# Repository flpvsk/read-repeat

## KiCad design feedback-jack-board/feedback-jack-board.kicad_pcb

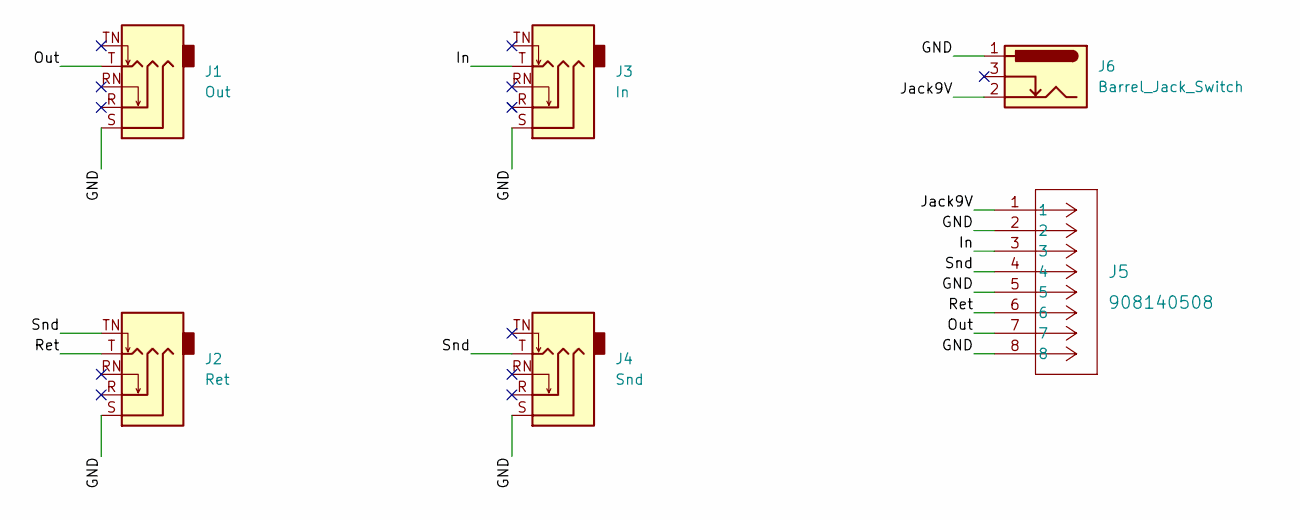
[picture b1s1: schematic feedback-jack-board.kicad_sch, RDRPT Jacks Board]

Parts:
J1: Out; tayda-A6446-6mm35-jack-pcb-compact
J2: Ret; tayda-A6446-6mm35-jack-pcb-compact
J3: In; tayda-A6446-6mm35-jack-pcb-compact
J4: Snd; tayda-A6446-6mm35-jack-pcb-compact
J5: 908140508; CONN_SDA-90814_08_MOL
J6: Barrel_Jack_Switch; BarrelJack_GCT_DCJ200-10-A_Horizontal

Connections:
/GND: J1.S, J2.S, J3.S, J4.S, J5.2, J5.5, J5.8, J6.1
/In: J3.T, J5.3
/Jack9V: J5.1, J6.2
/Out: J1.T, J5.7
/Ret: J2.T, J5.6
/Snd: J2.TN, J4.T, J5.4

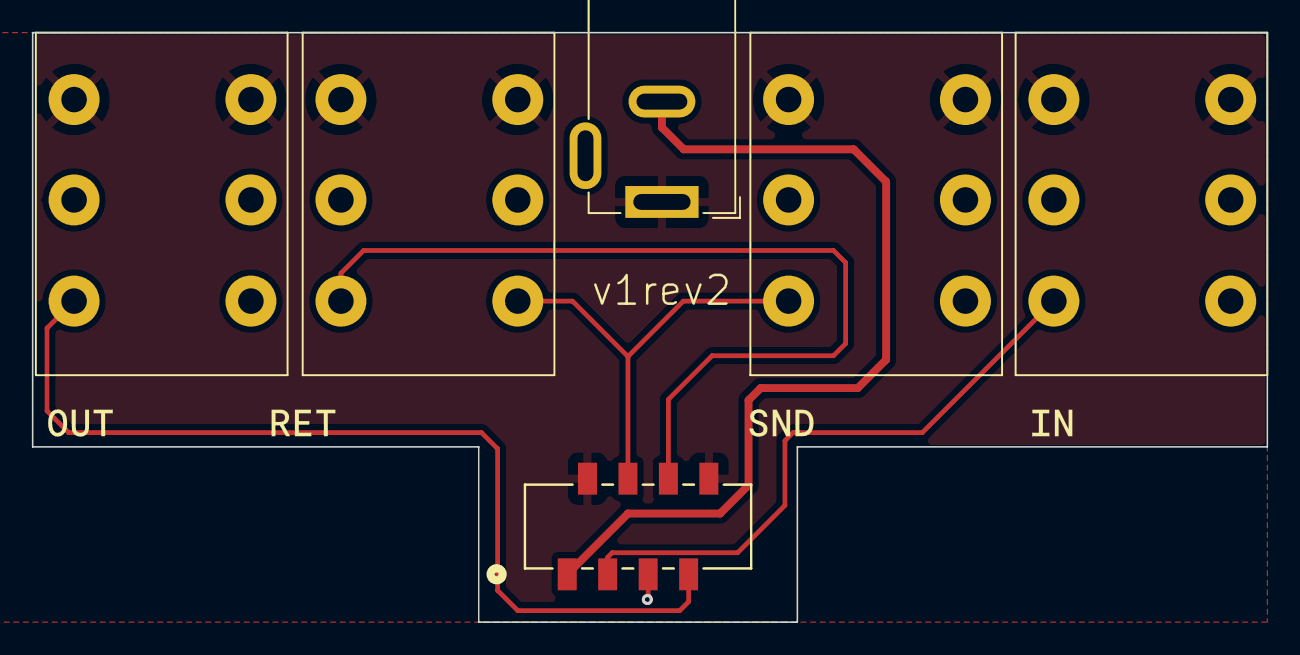
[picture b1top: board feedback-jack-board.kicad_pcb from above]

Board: 2 copper layers, 77.5 x 37.0 mm, 11 parts (1 on the bottom side), 6 nets.

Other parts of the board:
kibuzzard-67A4F1E7: G***; kibuzzard-67A4F1E7
kibuzzard-67A4F12B: G***; kibuzzard-67A4F12B
kibuzzard-67A4F13A: G***; kibuzzard-67A4F13A
kibuzzard-67A4F113: G***; kibuzzard-67A4F113
kibuzzard-67A4F143: G***; kibuzzard-67A4F143

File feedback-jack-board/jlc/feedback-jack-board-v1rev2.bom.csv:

"Comment","Designator","Footprint","LCSC"
"Out","J1","Tayda-A6446-6-35mm-Compact-PCB-Mounted-Jack:tayda-A6446-6mm35-jack-pcb-compact",""
"Ret","J2","Tayda-A6446-6-35mm-Compact-PCB-Mounted-Jack:tayda-A6446-6mm35-jack-pcb-compact",""
"In","J3","Tayda-A6446-6-35mm-Compact-PCB-Mounted-Jack:tayda-A6446-6mm35-jack-pcb-compact",""
"Snd","J4","Tayda-A6446-6-35mm-Compact-PCB-Mounted-Jack:tayda-A6446-6mm35-jack-pcb-compact",""
"908140508","J5","molex-picoflex8:CONN_SDA-90814_08_MOL",""
"Barrel_Jack_Switch","J6","Connector_BarrelJack:BarrelJack_GCT_DCJ200-10-A_Horizontal",""

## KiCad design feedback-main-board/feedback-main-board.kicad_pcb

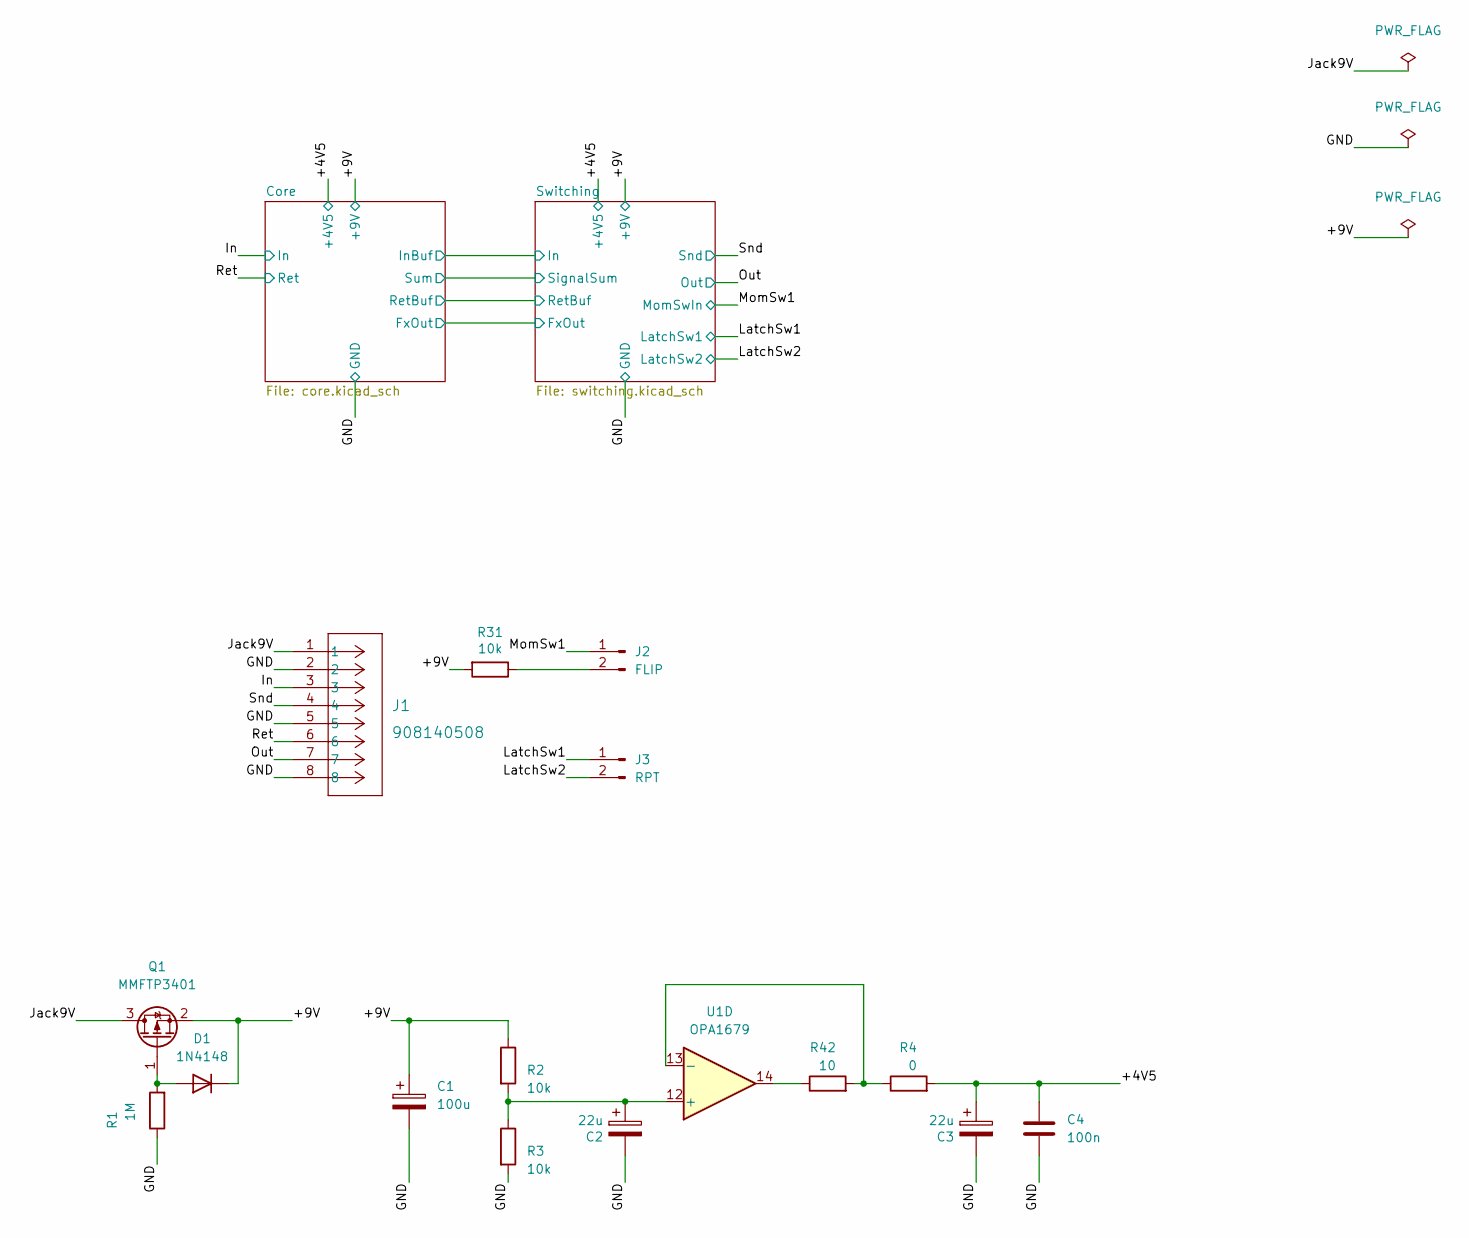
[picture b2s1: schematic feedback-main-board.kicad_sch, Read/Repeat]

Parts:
C1: 100u; CP_Elec_6.3x5.4; LCSC C2836437
C2, C3: 22u; CP_Elec_5x5.4; LCSC C23289
C4: 100n; C_0603_1608Metric_Pad1.08x0.95mm_HandSolder; Mouser 581-06035C105MAT2A
D1: 1N4148; D_SOD-323_HandSoldering; LCSC C6423741
J1: 908140508; CONN_SDA-90814_08_MOL; LCSC DNP
J2: FLIP; JST_XH_B2B-XH-A_1x02_P2.50mm_Vertical; LCSC DNP
J3: RPT; JST_XH_B2B-XH-A_1x02_P2.50mm_Vertical; LCSC DNP
Q1: MMFTP3401; SOT-23; LCSC C596234
R1: 1M; R_0603_1608Metric_Pad0.98x0.95mm_HandSolder; LCSC C22935
R2, R3, R31: 10k; R_0603_1608Metric_Pad0.98x0.95mm_HandSolder; LCSC C25804
R4: 0; R_0603_1608Metric_Pad0.98x0.95mm_HandSolder; LCSC C21189
R42: 10; R_0603_1608Metric_Pad0.98x0.95mm_HandSolder; LCSC C22859
U1: OPA1679; SOIC-14_3.9x8.7mm_P1.27mm; LCSC C2878631

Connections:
/+4V5: C3.1, C4.2, R4.2; also elsewhere on the board
/+9V: C1.1, D1.1 (K), Q1.2 (S), R2.1, R31.2; also elsewhere on the board
/GND: C1.2, C2.2, C3.2, C4.1, J1.2, J1.5, J1.8, R1.1, R3.2; also elsewhere on the board
/In: J1.3; also elsewhere on the board
/Jack9V: J1.1, Q1.3 (D)
/LatchSw1: J3.1; also elsewhere on the board
/LatchSw2: J3.2; also elsewhere on the board
/MomSw1: J2.1; also elsewhere on the board
/Out: J1.7; also elsewhere on the board
/Ret: J1.6; also elsewhere on the board
/Snd: J1.4; also elsewhere on the board
unnamed: D1.2 (A), Q1.1 (G), R1.2
unnamed: J2.2, R31.1
unnamed: R42.1, U1.14
unnamed: C2.1, R2.2, R3.1, U1.12 (+)
unnamed: R4.1, R42.2, U1.13 (-)

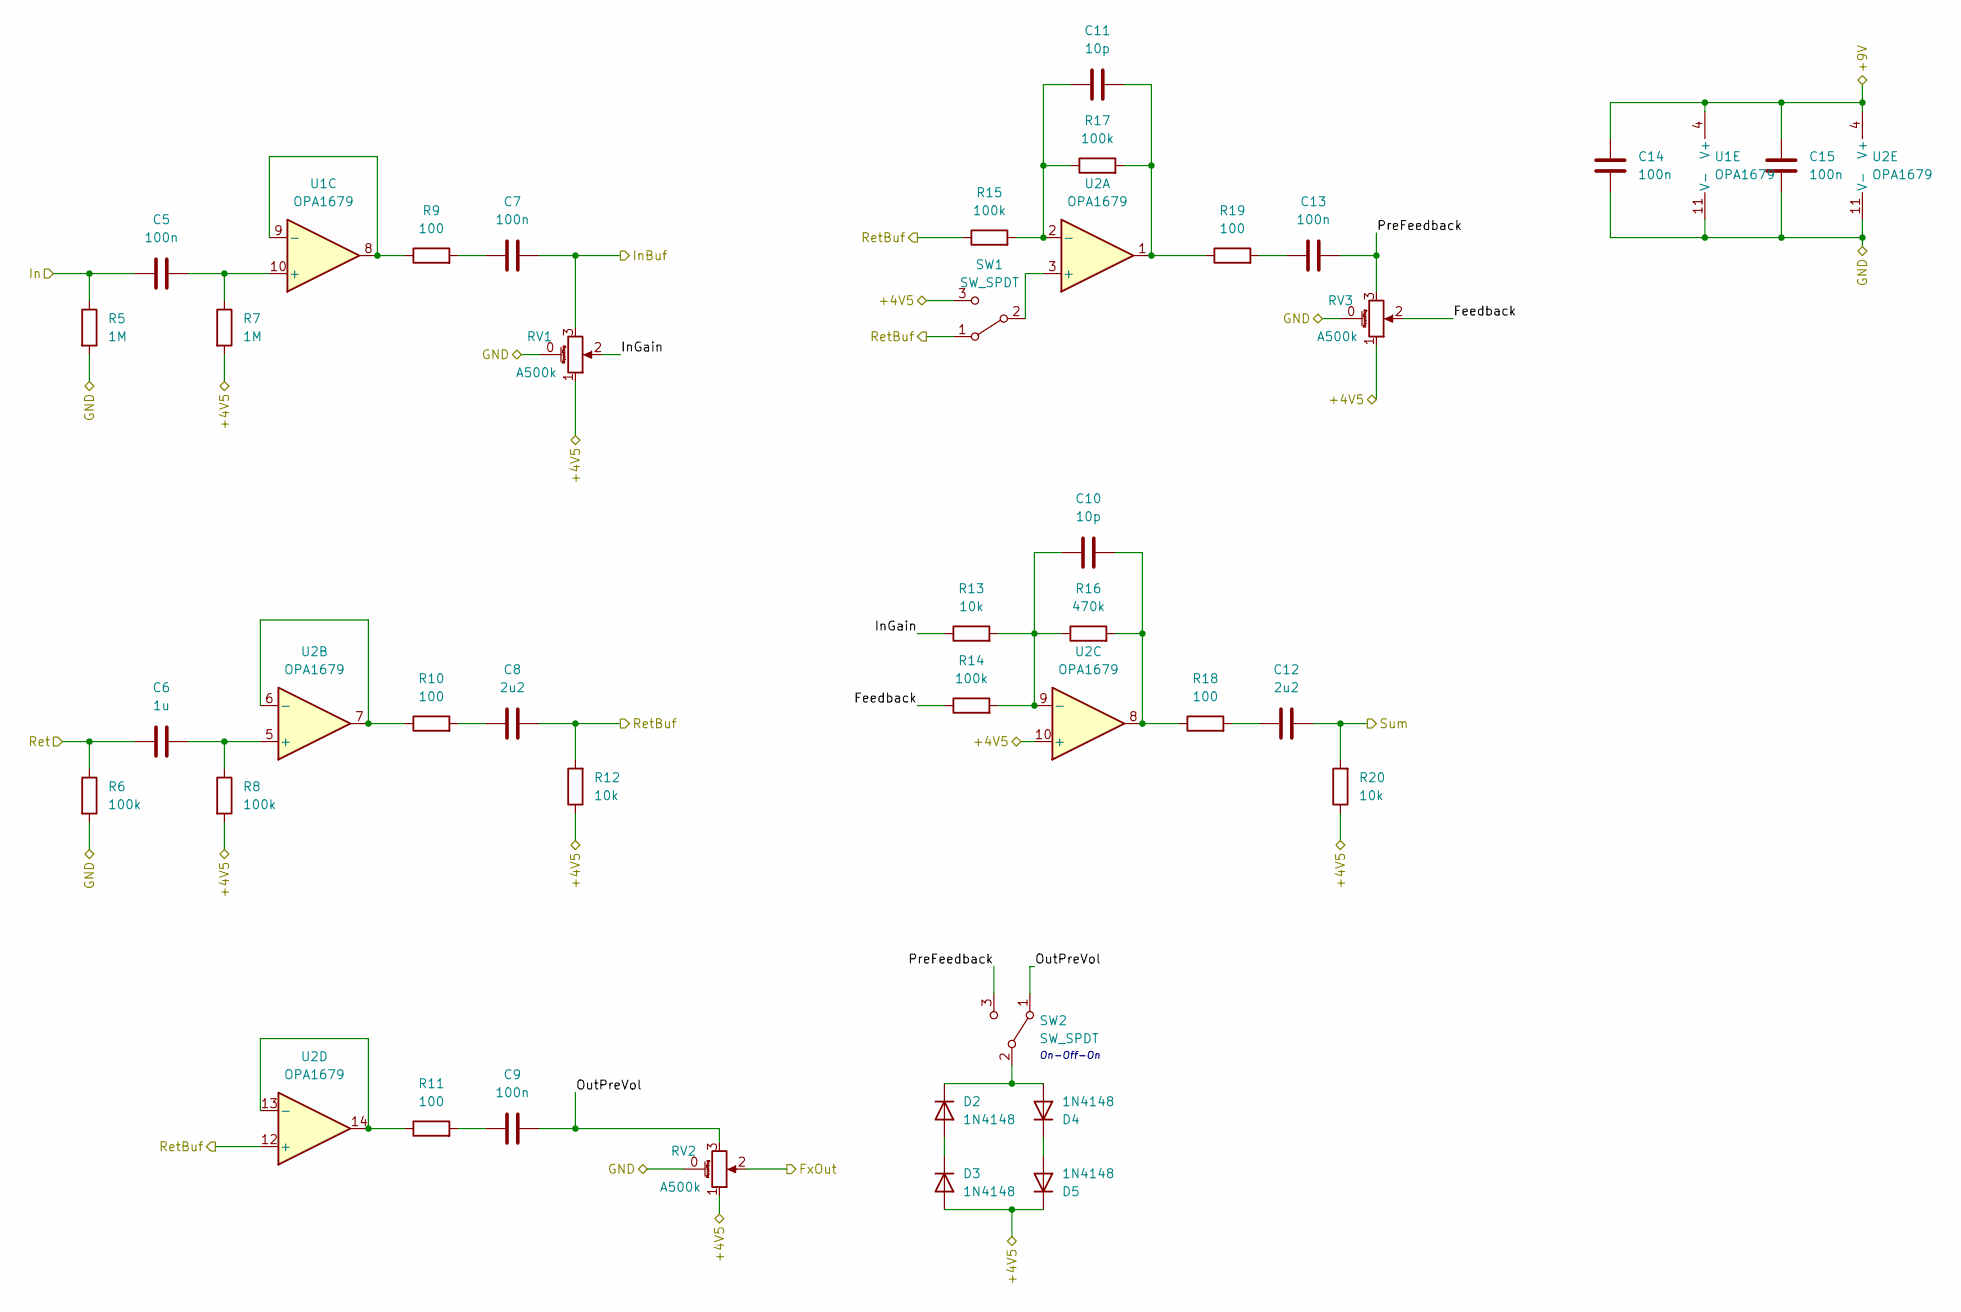
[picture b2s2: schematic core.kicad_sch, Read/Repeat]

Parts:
C5: 100n; C_Rect_L7.0mm_W2.5mm_P5.00mm; LCSC DNP
C6: 1u; C_Rect_L7.0mm_W4.5mm_P5.00mm; Mouser 505-MKS2-1/63/10A
C7, C9, C13: 100n; C_Rect_L7.2mm_W7.2mm_P5.00mm_FKS2_FKP2_MKS2_MKP2; Mouser 505-MKS22.2/63/5
C8, C12: 2u2; C_Rect_L7.2mm_W7.2mm_P5.00mm_FKS2_FKP2_MKS2_MKP2; Mouser 505-MKS22.2/63/5
C10, C11: 10p; C_0603_1608Metric_Pad1.08x0.95mm_HandSolder; LCSC C1634
C14, C15: 100n; C_0603_1608Metric_Pad1.08x0.95mm_HandSolder; Mouser 581-06035C105MAT2A
D2, D3, D4, D5: 1N4148; D_SOD-323; LCSC C2128
R5, R7: 1M; R_0603_1608Metric_Pad0.98x0.95mm_HandSolder; LCSC C22935
R6, R8, R14, R15, R17: 100k; R_0603_1608Metric_Pad0.98x0.95mm_HandSolder; LCSC C25803
R9, R10, R11, R18, R19: 100; R_0603_1608Metric_Pad0.98x0.95mm_HandSolder; LCSC C22775
R12, R13, R20: 10k; R_0603_1608Metric_Pad0.98x0.95mm_HandSolder; LCSC C25804
R16: 470k; R_0603_1608Metric_Pad0.98x0.95mm_HandSolder; LCSC C23178
RV1, RV2, RV3: A500k; V3_TRIM_R0904NB10KL-Keepout; LCSC DNP
SW1, SW2: SW_SPDT; SPDT.LUGS.PM; LCSC DNP
U1, U2: OPA1679; SOIC-14_3.9x8.7mm_P1.27mm; LCSC C2878631

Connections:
/+4V5: D3.2 (A), D5.1 (K), R7.2, R8.2, R12.1, R20.1, RV1.1, RV2.1, RV3.1, SW1.3 (C), U2.10 (+); also elsewhere on the board
/+9V: C14.2, C15.2, U1.4 (V+), U2.4 (V+); also elsewhere on the board
/Core/Feedback: R14.1, RV3.2
/Core/FxOut: RV2.2; also elsewhere on the board
/Core/InBuf: C7.2, RV1.3; also elsewhere on the board
/Core/InGain: R13.1, RV1.2
/Core/OutPreVol: C9.2, RV2.3, SW2.1 (A)
/Core/PreFeedback: C13.2, RV3.3, SW2.3 (C)
/Core/RetBuf: C8.2, R12.2, R15.1, SW1.1 (A), U2.12 (+); also elsewhere on the board
/Core/Sum: C12.2, R20.2; also elsewhere on the board
/GND: C14.1, C15.1, R5.2, R6.2, RV1.0 (ShieldPin), RV2.0 (ShieldPin), RV3.0 (ShieldPin), U1.11 (V-), U2.11 (V-); also elsewhere on the board
/In: C5.1, R5.1; also elsewhere on the board
/Ret: C6.1, R6.1; also elsewhere on the board
unnamed: C7.1, R9.2
unnamed: C8.1, R10.2
unnamed: C9.1, R11.2
unnamed: C10.2, R16.2, R18.1, U2.8
unnamed: C11.2, R17.2, R19.1, U2.1
unnamed: C12.1, R18.2
unnamed: C13.1, R19.2
unnamed: D2.2 (A), D3.1 (K)
unnamed: D2.1 (K), D4.2 (A), SW2.2 (B)
unnamed: D4.1 (K), D5.2 (A)
unnamed: SW1.2 (B), U2.3 (+)
unnamed: C5.2, R7.1, U1.10 (+)
unnamed: R9.1, U1.8, U1.9 (-)
unnamed: C11.1, R15.2, R17.1, U2.2 (-)
unnamed: C6.2, R8.1, U2.5 (+)
unnamed: R10.1, U2.6 (-), U2.7
unnamed: C10.1, R13.2, R14.2, R16.1, U2.9 (-)
unnamed: R11.1, U2.13 (-), U2.14

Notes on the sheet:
On-Off-On

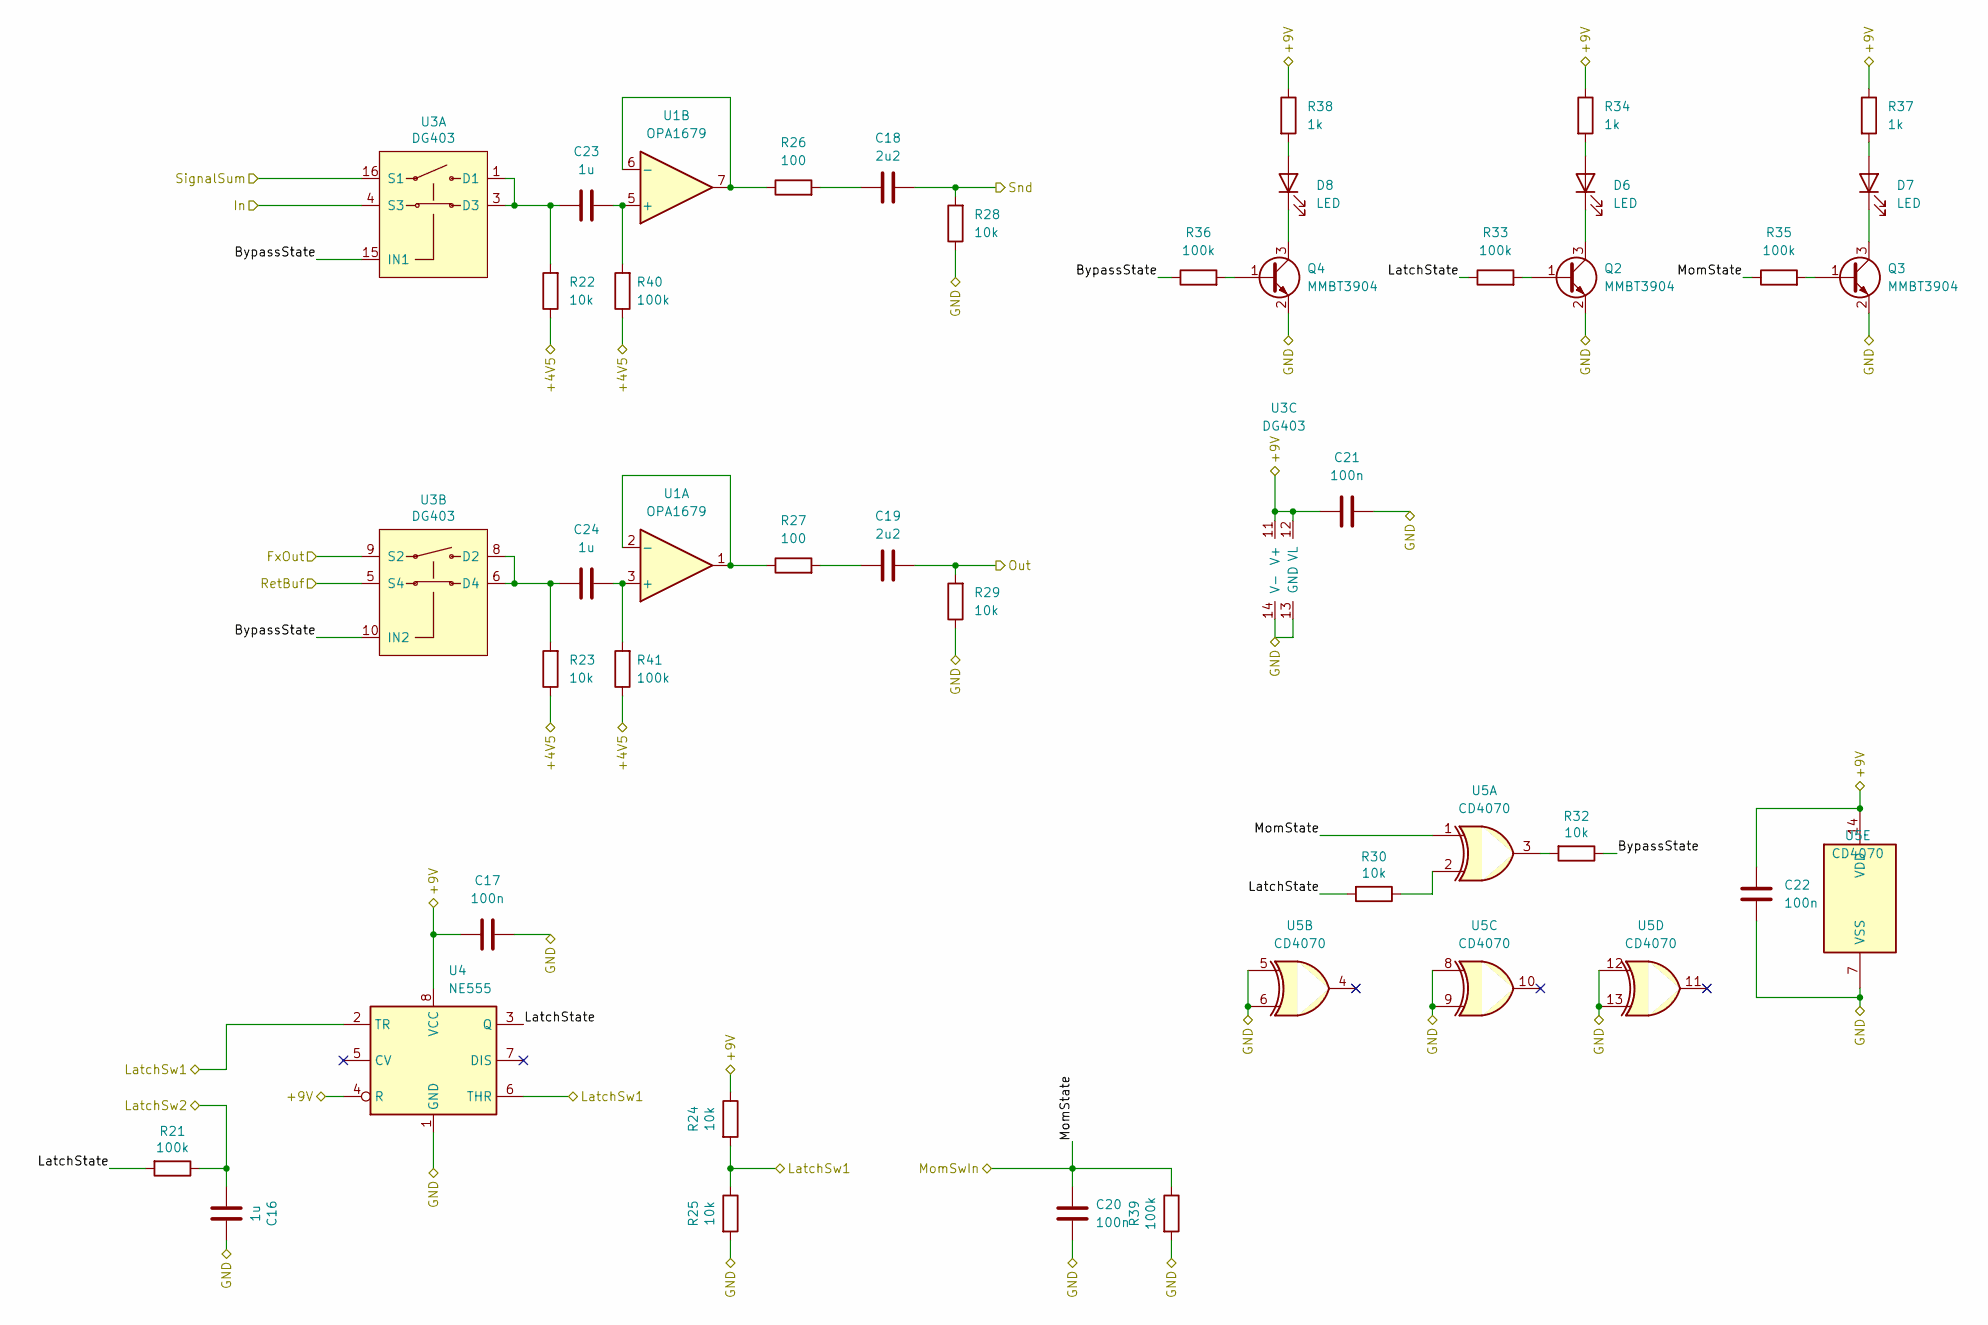
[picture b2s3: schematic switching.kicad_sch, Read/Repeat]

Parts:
C16: 1u; C_0603_1608Metric_Pad1.08x0.95mm_HandSolder; Mouser 581-06035C105MAT2A
C17, C20, C21, C22: 100n; C_0603_1608Metric_Pad1.08x0.95mm_HandSolder; Mouser 581-06035C105MAT2A
C18, C19: 2u2; C_Rect_L7.2mm_W7.2mm_P5.00mm_FKS2_FKP2_MKS2_MKP2; Mouser 505-MKS22.2/63/5
C23, C24: 1u; C_Rect_L7.0mm_W2.5mm_P5.00mm; LCSC DNP
D6, D7, D8: LED; LED_D5.0mm; LCSC DNP
Q2, Q3, Q4: MMBT3904; SOT-23; LCSC C20526
R21, R33, R35, R36, R39, R40, R41: 100k; R_0603_1608Metric_Pad0.98x0.95mm_HandSolder; LCSC C25803
R22, R23, R24, R25, R28, R29, R30, R32: 10k; R_0603_1608Metric_Pad0.98x0.95mm_HandSolder; LCSC C25804
R26, R27: 100; R_0603_1608Metric_Pad0.98x0.95mm_HandSolder; LCSC C22775
R34, R37, R38: 1k; R_0603_1608Metric_Pad0.98x0.95mm_HandSolder; LCSC C21190
U1: OPA1679; SOIC-14_3.9x8.7mm_P1.27mm; LCSC C2878631
U3: DG403; SOIC-16_3.9x9.9mm_P1.27mm; LCSC C145284
U4: NE555; SOIC-8_3.9x4.9mm_P1.27mm; LCSC C7593
U5: CD4070; SOIC-14_3.9x8.7mm_P1.27mm; Mouser 595-CD4070BM96E4

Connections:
/+4V5: R22.1, R23.1, R40.1, R41.1; also elsewhere on the board
/+9V: C17.1, C21.1, C22.2, R24.1, R34.1, R37.1, R38.1, U3.11 (V+), U3.12 (VL), U4.4 (R), U4.8 (VCC), U5.14 (VDD); also elsewhere on the board
/Core/FxOut: U3.9 (S2); also elsewhere on the board
/Core/InBuf: U3.4 (S3); also elsewhere on the board
/Core/RetBuf: U3.5 (S4); also elsewhere on the board
/Core/Sum: U3.16 (S1); also elsewhere on the board
/GND: C16.1, C17.2, C20.2, C21.2, C22.1, Q2.2 (E), Q3.2 (E), Q4.2 (E), R25.2, R28.1, R29.1, R39.2, U3.13 (GND), U3.14 (V-), U4.1 (GND), U5.5, U5.6, U5.7 (VSS), U5.8, U5.9, U5.12, U5.13; also elsewhere on the board
/LatchSw1: R24.2, R25.1, U4.2 (TR), U4.6 (THR); also elsewhere on the board
/LatchSw2: C16.2, R21.1; also elsewhere on the board
/MomSw1: C20.1, R35.1, R39.1, U5.1; also elsewhere on the board
/Out: C19.2, R29.2; also elsewhere on the board
/Snd: C18.2, R28.2; also elsewhere on the board
/Switching/BypassState: R32.1, R36.1, U3.10 (IN2), U3.15 (IN1)
/Switching/LatchState: R21.2, R30.2, R33.1, U4.3 (Q)
unnamed: C18.1, R26.2
unnamed: C19.1, R27.2
unnamed: D6.2 (A), R34.2
unnamed: D6.1 (K), Q2.3 (C)
unnamed: D7.2 (A), R37.2
unnamed: D7.1 (K), Q3.3 (C)
unnamed: D8.2 (A), R38.2
unnamed: D8.1 (K), Q4.3 (C)
unnamed: Q2.1 (B), R33.2
unnamed: Q3.1 (B), R35.2
unnamed: Q4.1 (B), R36.2
unnamed: R30.1, U5.2
unnamed: R32.2, U5.3
unnamed: C24.2, R41.2, U1.3 (+)
unnamed: R27.1, U1.1, U1.2 (-)
unnamed: C23.2, R40.2, U1.5 (+)
unnamed: R26.1, U1.6 (-), U1.7
unnamed: C23.1, R22.2, U3.1 (D1), U3.3 (D3)
unnamed: C24.1, R23.2, U3.6 (D4), U3.8 (D2)

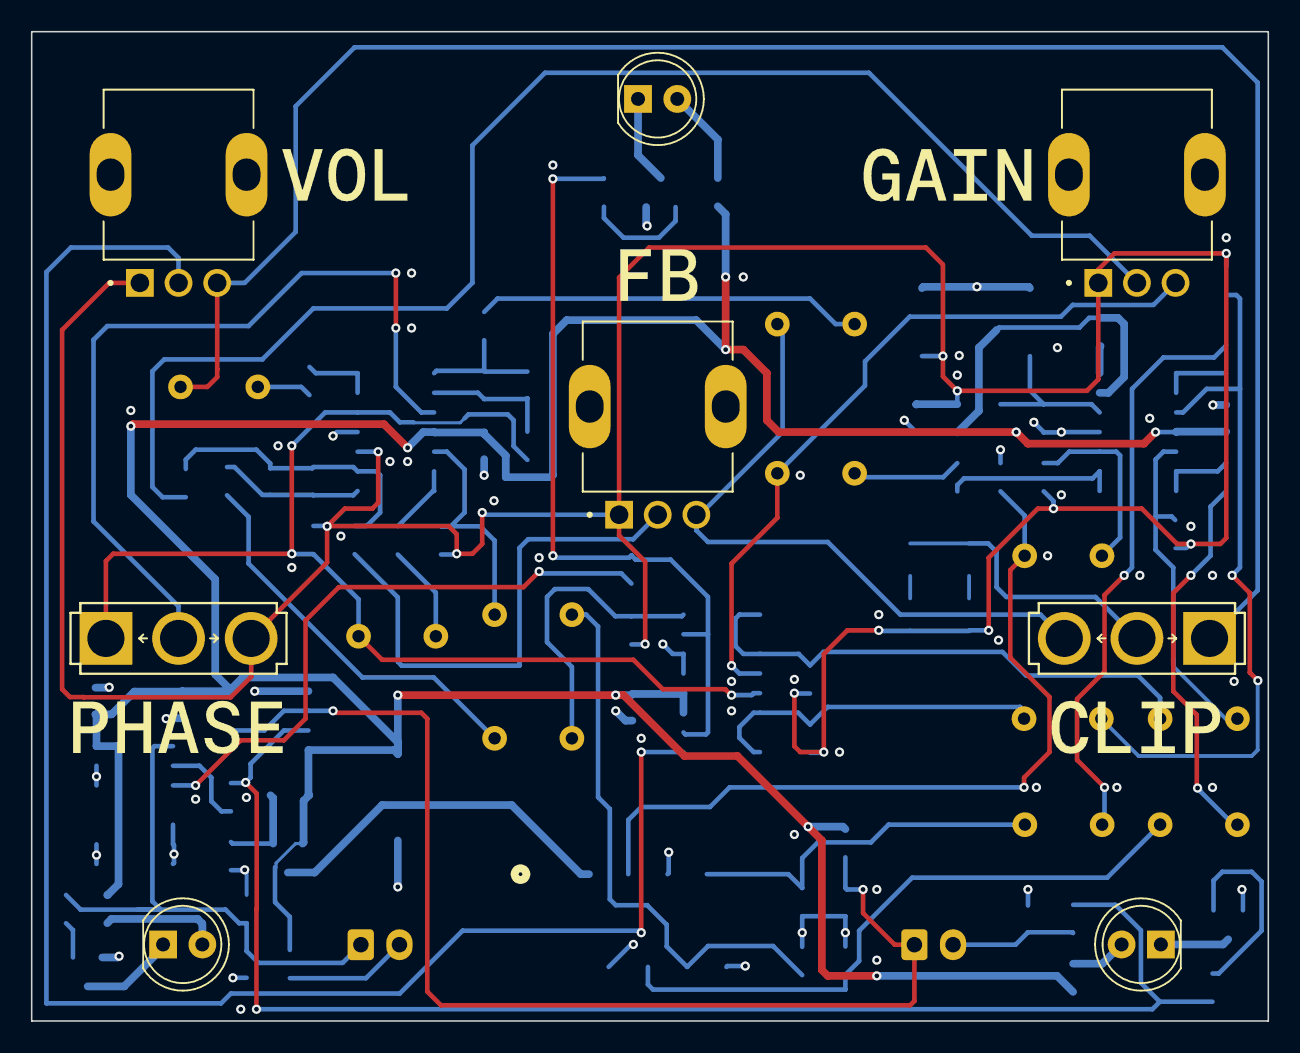
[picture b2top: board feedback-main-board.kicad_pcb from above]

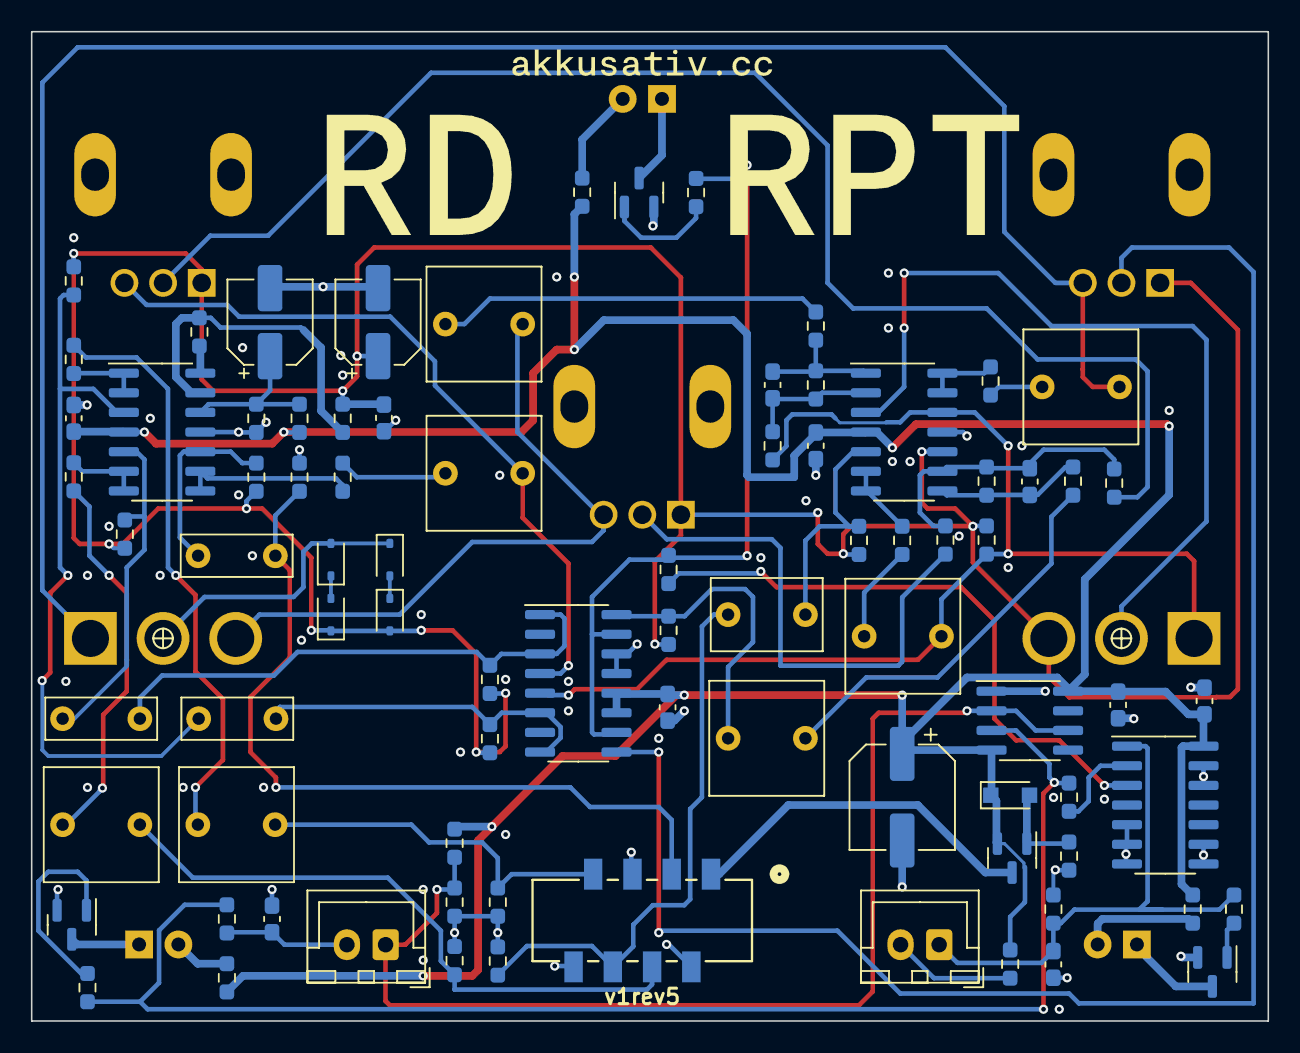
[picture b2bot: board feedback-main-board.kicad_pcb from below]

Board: 4 copper layers, 80.0 x 64.0 mm, 101 parts (86 on the bottom side), 63 nets.

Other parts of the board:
FLP: FLP; MOMENTARY
RPT: RPT; MOMENTARY
kibuzzard-67A4EAB6: G***; kibuzzard-67A4EAB6
kibuzzard-67A4EAD0: G***; kibuzzard-67A4EAD0
kibuzzard-67A4EB37: G***; kibuzzard-67A4EB37
kibuzzard-67A4EB98: G***; kibuzzard-67A4EB98
kibuzzard-67A4EBC1: G***; kibuzzard-67A4EBC1
kibuzzard-67A4EC3B: G***; kibuzzard-67A4EC3B
kibuzzard-67A4EC49: G***; kibuzzard-67A4EC49
kibuzzard-67A4EDCC: G***; kibuzzard-67A4EDCC

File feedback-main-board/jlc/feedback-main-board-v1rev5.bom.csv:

"Comment","Designator","Footprint","LCSC"
"100u","C1","Capacitor_SMD:CP_Elec_6.3x5.4","C2836437"
"22u","C2,C3","Capacitor_SMD:CP_Elec_5x5.4","C23289"
"100n","C4,C14,C15,C17,C20,C21,C22","Capacitor_SMD:C_0603_1608Metric_Pad1.08x0.95mm_HandSolder","C14663"
"100n","C5","Capacitor_THT:C_Rect_L7.0mm_W2.5mm_P5.00mm","DNP"
"1u","C6","Capacitor_THT:C_Rect_L7.0mm_W4.5mm_P5.00mm","DNP"
"100n","C7,C9,C13","Capacitor_THT:C_Rect_L7.2mm_W7.2mm_P5.00mm_FKS2_FKP2_MKS2_MKP2","DNP"
"2u2","C8,C12,C18,C19","Capacitor_THT:C_Rect_L7.2mm_W7.2mm_P5.00mm_FKS2_FKP2_MKS2_MKP2","DNP"
"10p","C10,C11","Capacitor_SMD:C_0603_1608Metric_Pad1.08x0.95mm_HandSolder","C1634"
"1u","C16","Capacitor_SMD:C_0603_1608Metric_Pad1.08x0.95mm_HandSolder","C15849"
"1u","C23,C24","Capacitor_THT:C_Rect_L7.0mm_W2.5mm_P5.00mm","DNP"
"1N4148","D1","Diode_SMD:D_SOD-323_HandSoldering","C6423741"
"1N4148","D2,D3,D4,D5","Diode_SMD:D_SOD-323","C2128"
"LED","D6,D7,D8","LED_THT:LED_D5.0mm","DNP"
"908140508","J1","molex-picoflex8:CONN_SDA-90814_08_MOL","DNP"
"FLIP","J2","Connector_JST:JST_XH_B2B-XH-A_1x02_P2.50mm_Vertical","DNP"
"RPT","J3","Connector_JST:JST_XH_B2B-XH-A_1x02_P2.50mm_Vertical","DNP"
"MMFTP3401","Q1","Package_TO_SOT_SMD:SOT-23","C596234"
"MMBT3904","Q2,Q3,Q4","Package_TO_SOT_SMD:SOT-23","C20526"
"1M","R1,R5,R7","Resistor_SMD:R_0603_1608Metric_Pad0.98x0.95mm_HandSolder","C22935"
"10k","R2,R3,R12,R13,R20,R22,R23,R24,R25,R28,R29,R30,R31,R32","Resistor_SMD:R_0603_1608Metric_Pad0.98x0.95mm_HandSolder","C25804"
"0","R4","Resistor_SMD:R_0603_1608Metric_Pad0.98x0.95mm_HandSolder","C21189"
"100k","R6,R8,R14,R15,R17,R21,R33,R35,R36,R39,R40,R41","Resistor_SMD:R_0603_1608Metric_Pad0.98x0.95mm_HandSolder","C25803"
"100","R9,R10,R11,R18,R19,R26,R27","Resistor_SMD:R_0603_1608Metric_Pad0.98x0.95mm_HandSolder","C22775"
"470k","R16","Resistor_SMD:R_0603_1608Metric_Pad0.98x0.95mm_HandSolder","C23178"
"1k","R34,R37,R38","Resistor_SMD:R_0603_1608Metric_Pad0.98x0.95mm_HandSolder","C21190"
"10","R42","Resistor_SMD:R_0603_1608Metric_Pad0.98x0.95mm_HandSolder","C22859"
"A500k","RV1,RV2,RV3","Pots:V3_TRIM_R0904NB10KL-Keepout","DNP"
"SW_SPDT","SW1,SW2","MBP switches:SPDT.LUGS.PM","DNP"
"OPA1679","U1,U2","Package_SO:SOIC-14_3.9x8.7mm_P1.27mm","C2878631"
"DG403","U3","Package_SO:SOIC-16_3.9x9.9mm_P1.27mm","C145284"
"NE555","U4","Package_SO:SOIC-8_3.9x4.9mm_P1.27mm","C7593"
"CD4070","U5","Package_SO:SOIC-14_3.9x8.7mm_P1.27mm","C28329"

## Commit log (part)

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2025-01-24 Schem draft
2025-01-26 Pre remove gain
2025-01-26 Back to gain/vol
2025-01-27 Jack board
2025-01-29 Design wip
2025-01-29 Volume bypass wip
2025-01-29 Switching fixes from breadboarding pre-CD4070
2025-02-05 Board started
2025-02-06 Component placement
2025-02-06 Routing v1 done
2025-02-06 Rotate molex connector properly
2025-02-06 Main PCB done
2025-02-06 Jacks board layout
2025-02-06 Main v1rev1 ordered at Aisler
2025-02-06 Jacks board ordered at aisler
2025-02-06 Mouser parts ordered
2025-02-22 rev2 wip start
2025-02-23 Wip rev2
2025-02-24 Updates for rev2 schematic
2025-02-24 rev2 main board layout getting close
2025-02-25 Jack board updates
2025-02-25 Tayda template v1rev2
2025-02-25 Design updates
2025-03-09 Move clipping to pre-feedback
2025-03-14 Changes pre-rev3
2025-03-18 JLCPCB rev3 ordered
2025-03-29 Virtual BOM generated
2025-05-19 Main rev4 ordered
2025-05-22 Added note about larger pots
